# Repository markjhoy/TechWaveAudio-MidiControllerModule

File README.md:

# [TechWave Audio MIDI to CV Module](https://techwaveaudio.com/techwave-audio-mcm-100-midi-to-cv-eurorack-module/) : MCM-100

A monophonic MIDI controller Eurorack module using the Raspberry Pi Pico (RP2040).

Brought to you by [TechWave Audio](https://techwaveaudio.com)

## Features
* Single or omni MIDI channel input
* MIDI input via class-compliant USB-C or standard 5-pin MIDI cable
* Four CV outputs for note (1v/oct), Velocity, assignable Out 1 and Out 2 
  * 1v/octave through 10 octaves (at 0 to +10v), or 5 octaves (at 0 to +5v)
  * Two CV outputs with flexible routing
  * All CV outputs voltage selectable from 0v to +10v or 0 to +5v
* Expandable with additional four flexible-routed CV outputs.
* Gate, trigger, and clock full 0 to +5v outputs with divisible clock sync ticks
* Selectable note priority (last, highest, lowest)
* Tuneable pitch and velocity adjust
* Customizable trigger output duration pulse width
* Pitch bend response range from 0 to 5 octaves
* Real time display of note and output states
* Settings persist to on-board flash ROM
* 6hp wide, 3U height
* Max Power Draw:
  * +12v: 72mA (80mA with expansion) 
  * -12v: 15mA (20mA with expansion)
  * +5v: 0mA

---

### Responds to the following MIDI messages:

* **Note on / off**: sends/stops the note and velocity outputs.
  * Sends a trigger pulse on note on, and turns on the gate for the duration of the note.
  * For +10v output, responds to C-1 (note number 0) to B9 (note number 119).
  * For +5v output, responds to C2 (middle-C, note number 36) to B6 (note number 95).
* **Volume**: increases or decreases the velocity output.
* **Pitch bend**: modifies any currently playing note. Adjustable range from 0 to 5 octaves. 
* **Sustain**: holds a note on while the sustain is active.
* **Aftertouch**: selectable as an aux and/or control output.
* **Expression**: selectable as an aux and/or control output.
* **Mod wheel**: selectable as an aux and/or control output.
* **Effect 1**: selectable as an aux and/or control output.
* **Effect 2**: selectable as an aux and/or control output.
* **Start** and **Continue** sequence: selectable as an aux and/or control output.
* **Stop** sequence: selectable as an aux and/or control output.
* **Mute** (all notes off): clears any note, velocity, and gate outputs.
* **Clock tick**: MIDI clock ticks are sent directly to the `Clock` output and can be routed as an aux and/or control output.
* **Reset**: reset the MIDI input messaging queue and stops any output.

---

### Inputs

* **MIDI in**: single channel or respond to all channels (omni)
  * Both MIDI via UART and USB MIDI device in (as of v1.2.0) 
* **Menu navigation**: Five way switch (up/down, left/right, push enter)

--- 
### Outputs

* Four CV outputs:
  * **Note**: 0 to 10v output (selectable to 0 to 5v) for CV with 1v per octave.
  * **Velocity**: 0 to 10v output (selectable to 0 to 5v) for velocity / volume
  * **Out 1**: customizable CV output (0v to +10v max, selectable to 0v to +5v)
  * **Out 2**: customizable CV output (0v to +10v max, selectable to 0v to +5v)
* **Trigger**: single pulse when a note turns on, with customizable pulse on time (high / low level output)
* **Gate**: signal goes high while a note is on (high / low level output)
* **Clock**: 1ms pulse with each MIDI clock tick (high / low level output). Selectable to various clock divisions.

Using the MCM-100-EX Expansion Module, you can also add an additional four assignable CV outputs.

---

### Power

This module requires a full 16 pin (2x08 connector) standard Eurorack power connection as it uses both +/- 12v lines as well as the +5v source. 
Optional selectors in the hardware (via a DIP switch) allow the note signal to pass through to the CV bus line, and the gate signal as well.

Be certain when you plug the connector in that the orientation is the correct way, with the -12v line on the bottom (usually with the red stripe).

---

## Usage

On startup, you should see the boot screen with the current version:

The note and clock LEDs should turn on and off a few times before the dashboard screen is shown and the module is ready to be used.

The user manual can be found on the [TechWave Audio website](https://techwaveaudio.com/support/manuals/MCM-100-User_Manual.pdf).

### Dashboard

The dashboard shows the status of the current MIDI channel that it is listening on, as well as various outputs:
* The note and octave
* `vel`: The current velocity (corresponding to 0v to +10/+5v)
* `o1`: The current Out 1 value (corresponding to 0v to +10/+5v)
* `o2`: The current Out 2 value (corresponding to 0v to +10/+5v)
* Indicators for the state of the trigger, gate, and clock

If the MCM-100-EX expansion module is attached, additionally it will show:
* `x1`: The current Out X1 value (corresponding to 0v to +10/+5v)
* `x2`: The current Out X2 value (corresponding to 0v to +10/+5v)
* `x3`: The current Out X3 value (corresponding to 0v to +10/+5v)
* `x4`: The current Out X4 value (corresponding to 0v to +10/+5v)

While using the module, you can turn the dashboard display on and off via the display settings menu.
You can also adjust how often the display refreshes (set to a longer time if display events start to get dropped, shorter time for more frequent updates).

### Settings Menu

There are numerous settings available from the settings menu.
Pressing the encoder button on the dashboard display (regardless if the display is visible or not) will enter the menu.
See the [Menu System](./docs/MENU_SYSTEM.md) documentation for the menu system details.

**Note**: any settings are not persisted until you exit the menu back to the dashboard (with the exception of when resetting the settings to default).

## Building the Firmware From Source

### Prerequisites

* [Raspberry Pi Pico SDK](https://github.com/raspberrypi/pico-sdk)
* CMake
* Your favourite C++ compiler
* A compatible toolchain for building Pico firmware

### Setup

1. Initialize the Git submodules:
   1. run: `git submodule init`
   2. run: `git submodule update`
2. Copy the `.env.cmake.sample` to `.env.cmake`
3. Edit your `.env.cmake` for the following variables:
```
PICO_SDK_PATH {the path to the PICO_SDK directory)
PICO_TOOLCHAIN_PATH (path to the pico toolchain for your build machine)

# You should _not_ have to change the following
set(PICO_PLATFORM rp2040)
set(PICO_BOARD pico)
```

### Build script
```
./build.sh
```

This will run the full clean and build.

The firmware file will be put in:
```
./dist/TechWaveAudio-MCM-v2.0.0.uf2
```

## Firmware Updates

For this, you'll need a [firmware release](https://github.com/TechWave-Audio/TechWaveAudio-MidiControllerModule/releases) (or build your on locally), as well as a USB cable that has a micro-usb port on one end.

1.	Power off your rack.
2.	Remove the module from your rack but keep the module plugged in via the power cable.
3.	Download the desired firmware file version from the GitHub repository [firmware release](https://github.com/TechWave-Audio/TechWaveAudio-MidiControllerModule/releases). You only need to download the file with the .uf2 extension.
4.	Plug your USB-C cable into the jack on the front of the module and the other end into the computer with the firmware.
5.	While holding down the small boot select (BOOTSEL) button on the board, power on the module. Keep holding the boot select button until the module appears on your computer. The on-board Raspberry Pi Pico board will appear as a mass storage device, usually named “RPI-RP2”
6.	Copy the downloaded firmware .uf2 file to the storage device. When complete, the module should reboot.
7.	Power off your rack again.
8.	Disconnect your USB cable from the module and your computer. Your computer may give you a warning about the device not being properly ejected. You can safely ignore this warning.
9.	Put the module back into your rack and power back on.

Note that any settings you many have modified will be reset to any default.

## Design

## Schematic, PCB, and hardware

See the [hardware design](./docs/HARDWARE_DESIGN.md) documentation for information on the schematic and PCB design for the module.

Note - all files provided including KiCad designs and any gerber files are provided as-is and to be used at your own risk.
TechWave Audio does not guarantee the accuracy or any correctness of these files.
See the [HW_LICENSE license file](./HW_LICENSE.txt) for more, specifically the section "6 DISCLAIMER AND LIABILITY".

## Licensing

Software in this repository is licensed under the [BSD-3 License](LICENSE.txt). By using or contributing content to this repository you are agreeing to place your contributions under this license.

Hardware designs for this repository are [licensed under the CERN-OHL-S](HW_LICENSE.txt) ([CERN Open Hardware License](https://cern-ohl.web.cern.ch/)).

Parts of this repository may reference, depend on, or use compiled third party libraries. See [NOTICE.txt](NOTICE.txt) for additional details.

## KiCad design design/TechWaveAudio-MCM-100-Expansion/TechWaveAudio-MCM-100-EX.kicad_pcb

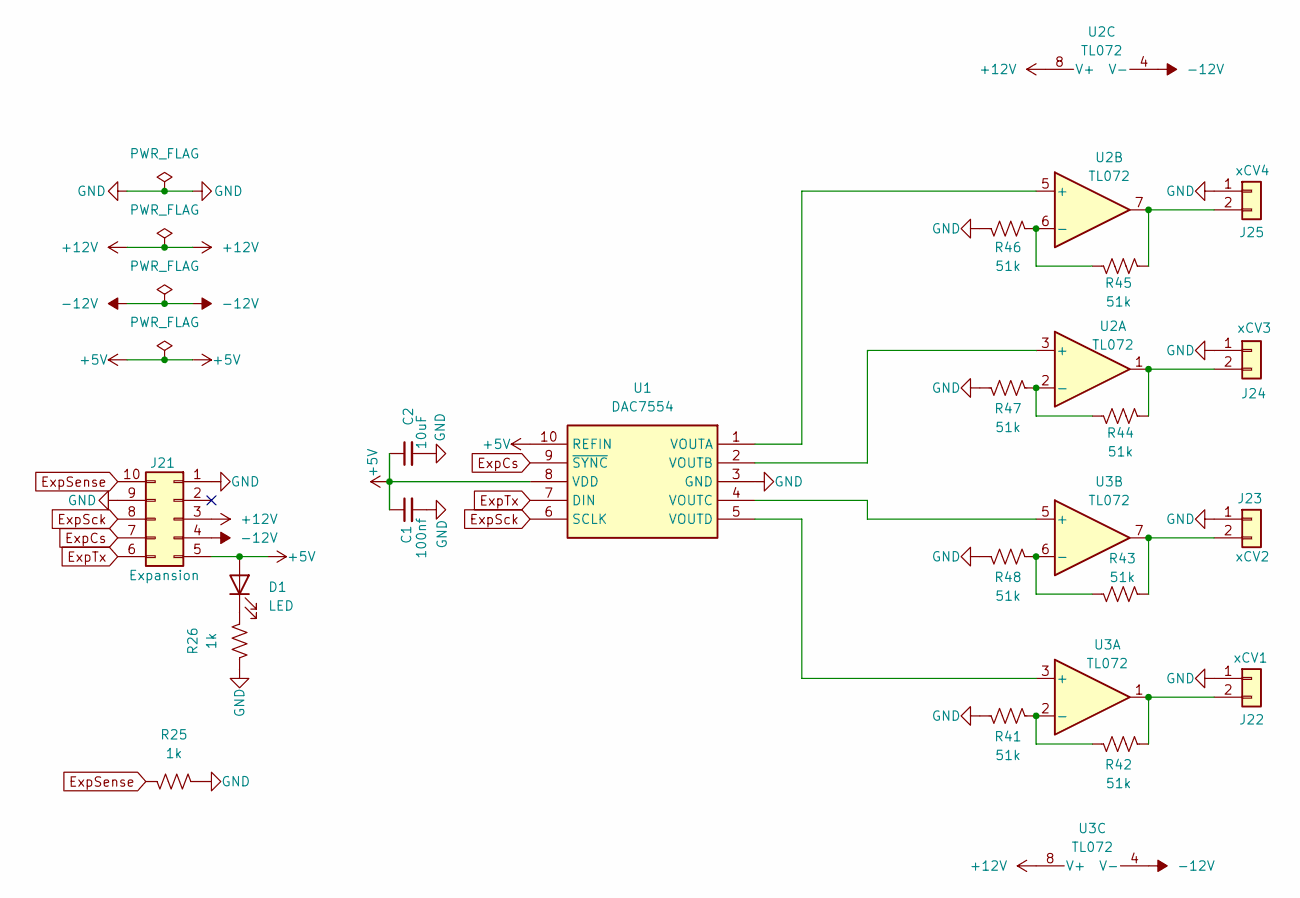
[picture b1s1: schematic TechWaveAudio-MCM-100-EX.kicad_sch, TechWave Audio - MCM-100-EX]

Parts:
C1: 100nf; C_0402_1005Metric; Voltage 1kV; Tolerance 100%
C2: 10uF; C_0805_2012Metric; Voltage 1kV; Tolerance 100%
D1: LED; LED_D3.0mm
J21: Expansion; IDC-Header_2x05_P2.54mm_Vertical
J22: xCV1; Audio_Jack_3.5mm_SameSky_SJ3-3505x
J23: xCV2; Audio_Jack_3.5mm_SameSky_SJ3-3505x
J24: xCV3; Audio_Jack_3.5mm_SameSky_SJ3-3505x
J25: xCV4; Audio_Jack_3.5mm_SameSky_SJ3-3505x
R25, R26: 1k; R_0402_1005Metric
R41, R42, R43, R44, R45, R46, R47, R48: 51k; R_0402_1005Metric
U1: DAC7554; MSOP-10_3x3mm_P0.5mm; Mouser Part Number 595-DAC7554IDGSR
U2, U3: TL072; SOIC-8_3.9x4.9mm_P1.27mm

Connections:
+5V: C1.1, C2.1, D1.2 (A), J21.5, U1.8 (VDD), U1.10 (REFIN)
+12V: J21.3, U2.8 (V+), U3.8 (V+)
-12V: J21.4, U2.4 (V-), U3.4 (V-)
ExpCs: J21.7, U1.9 (~SYNC)
ExpSck: J21.8, U1.6 (SCLK)
ExpSense: J21.10, R25.2
ExpTx: J21.6, U1.7 (DIN)
GND: C1.2, C2.2, J21.1, J21.9, J22.1, J23.1, J24.1, J25.1, R25.1, R26.2, R41.2, R46.2, R47.2, R48.2, U1.3 (GND)
unnamed: D1.1 (K), R26.1
unnamed: J22.2, R42.1, U3.1
unnamed: J23.2, R43.1, U3.7
unnamed: J24.2, R44.1, U2.1
unnamed: J25.2, R45.1, U2.7
unnamed: U1.1 (VOUTA), U2.5 (+)
unnamed: U1.2 (VOUTB), U2.3 (+)
unnamed: U1.4 (VOUTC), U3.5 (+)
unnamed: U1.5 (VOUTD), U3.3 (+)
unnamed: R44.2, R47.1, U2.2 (-)
unnamed: R45.2, R46.1, U2.6 (-)
unnamed: R41.1, R42.2, U3.2 (-)
unnamed: R43.2, R48.1, U3.6 (-)

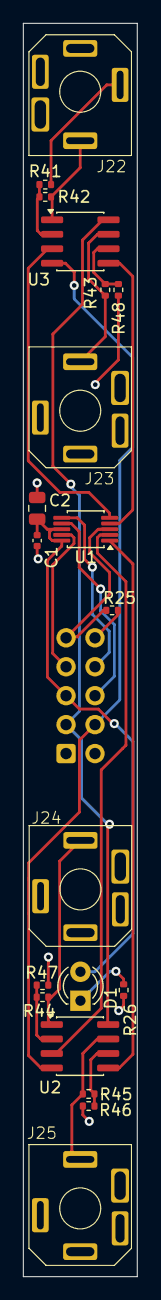
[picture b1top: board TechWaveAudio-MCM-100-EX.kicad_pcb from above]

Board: 2 copper layers, 10.0 x 110.0 mm, 21 parts (1 on the bottom side), 21 nets.

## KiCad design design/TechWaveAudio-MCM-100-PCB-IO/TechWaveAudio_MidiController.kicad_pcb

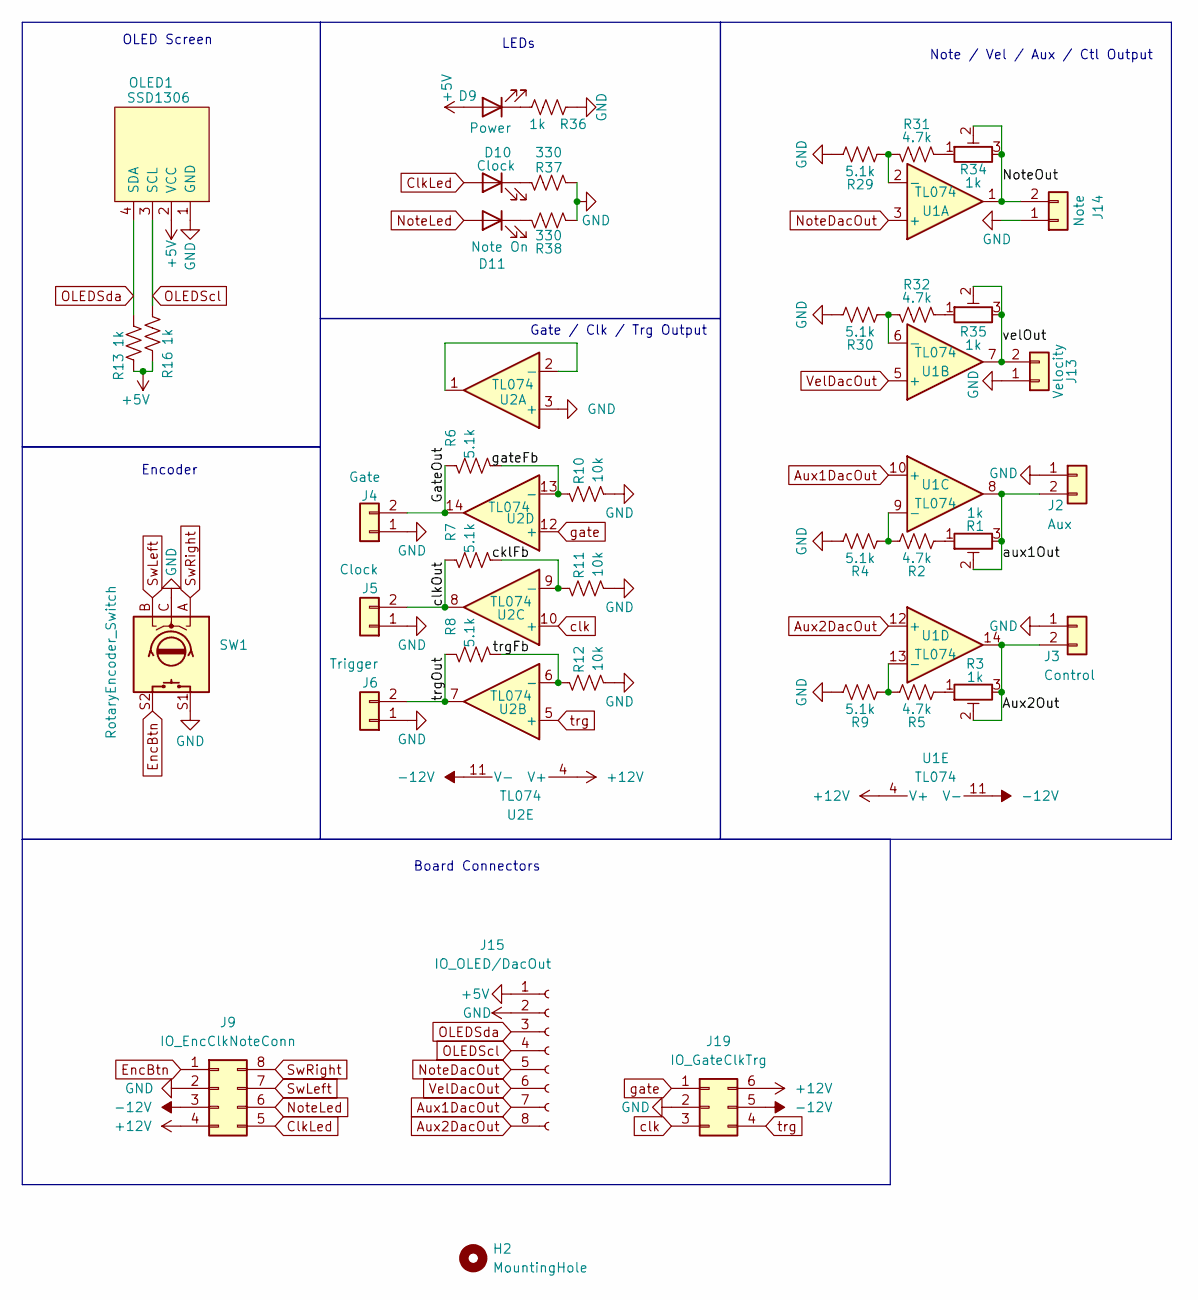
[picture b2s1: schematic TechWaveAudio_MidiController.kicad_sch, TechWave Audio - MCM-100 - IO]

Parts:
D9: Power; LED_D3.0mm
D10: Clock; LED_D3.0mm
D11: Note On; LED_D3.0mm
H2: MountingHole; MountingHole_3.2mm_M3
J2: Aux; Audio_Jack_3.5mm_SameSky_SJ3-3505x
J3: Control; Audio_Jack_3.5mm_SameSky_SJ3-3505x
J4: Gate; Audio_Jack_3.5mm_SameSky_SJ3-3505x
J5: Clock; Audio_Jack_3.5mm_SameSky_SJ3-3505x
J6: Trigger; Audio_Jack_3.5mm_SameSky_SJ3-3505x
J9: IO_EncClkNoteConn; PinSocket_2x04_P2.54mm_Vertical
J13: Velocity; Audio_Jack_3.5mm_SameSky_SJ3-3505x
J14: Note; Audio_Jack_3.5mm_SameSky_SJ3-3505x
J15: IO_OLED/DacOut; PinSocket_1x08_P2.54mm_Vertical
J19: IO_GateClkTrg; PinSocket_2x03_P2.54mm_Vertical
OLED1: SSD1306; PinSocket_1x04_P2.54mm_Vertical
R1, R3, R34, R35: 1k; Potentiometer_Bourns_3296X_Horizontal
R2, R5, R31, R32: 4.7k; R_0402_1005Metric
R4, R6, R7, R8, R9, R29, R30: 5.1k; R_0402_1005Metric
R10, R11, R12: 10k; R_0402_1005Metric
R13, R16, R36: 1k; R_0402_1005Metric
R37, R38: 330; R_0402_1005Metric
SW1: RotaryEncoder_Switch; Rotary_Encoder-PEC11-Breakout_Board
U1, U2: TL074; SOIC-14_3.9x8.7mm_P1.27mm

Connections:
+5V: D9.2 (A), J15.2, OLED1.2 (VCC), R13.1, R16.1
+12V: J9.4, J19.6, U1.4 (V+), U2.4 (V+)
-12V: J9.3, J19.5, U1.11 (V-), U2.11 (V-)
/Aux2Out: J3.2, R3.2, R3.3, U1.14
/GateOut: J4.2, R6.1, U2.14
/NoteOut: J14.2, R34.2, R34.3, U1.1
/aux1Out: J2.2, R1.2, R1.3, U1.8
/cklFb: R7.2, R11.1, U2.9 (-)
/clkOut: J5.2, R7.1, U2.8
/gateFb: R6.2, R10.1, U2.13 (-)
/trgFb: R8.2, R12.1, U2.6 (-)
/trgOut: J6.2, R8.1, U2.7
/velOut: J13.2, R35.2, R35.3, U1.7
Aux1DacOut: J15.7, U1.10 (+)
Aux2DacOut: J15.8, U1.12 (+)
ClkLed: D10.2 (A), J9.5
EncBtn: J9.1, SW1.S2
GND: J2.1, J3.1, J4.1, J5.1, J6.1, J9.2, J13.1, J14.1, J15.1, J19.2, OLED1.1 (GND), R4.1, R9.1, R10.2, R11.2, R12.2, R29.1, R30.1, R36.2, R37.2, R38.2, SW1.C, SW1.S1, U2.3 (+)
unnamed: D9.1 (K), R36.1
unnamed: D10.1 (K), R37.1
unnamed: D11.1 (K), R38.1
unnamed: R1.1, R2.2
unnamed: R3.1, R5.2
unnamed: R31.2, R34.1
unnamed: R32.2, R35.1
unnamed: R29.2, R31.1, U1.2 (-)
unnamed: R30.2, R32.1, U1.6 (-)
unnamed: R2.1, R4.2, U1.9 (-)
unnamed: R5.1, R9.2, U1.13 (-)
unnamed: U2.1, U2.2 (-)
NoteDacOut: J15.5, U1.3 (+)
NoteLed: D11.2 (A), J9.6
OLEDScl: J15.4, OLED1.3 (SCL), R16.2
OLEDSda: J15.3, OLED1.4 (SDA), R13.2
SwLeft: J9.7, SW1.B
SwRight: J9.8, SW1.A
VelDacOut: J15.6, U1.5 (+)
clk: J19.3, U2.10 (+)
gate: J19.1, U2.12 (+)
trg: J19.4, U2.5 (+)

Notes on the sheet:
Board Connectors
Note / Vel / Aux / Ctl Output
Encoder
Gate / Clk / Trg Output
OLED Screen
LEDs

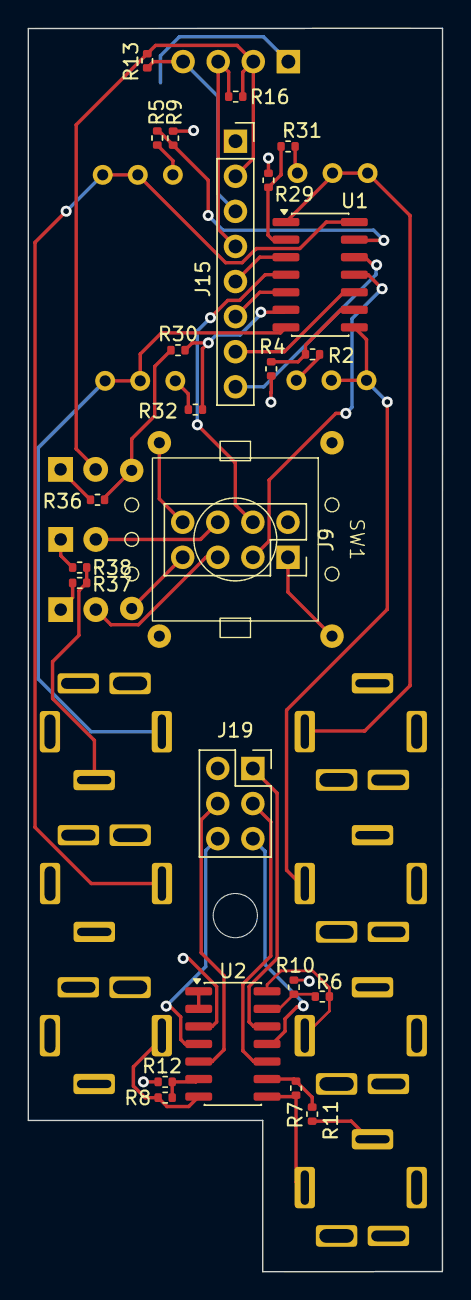
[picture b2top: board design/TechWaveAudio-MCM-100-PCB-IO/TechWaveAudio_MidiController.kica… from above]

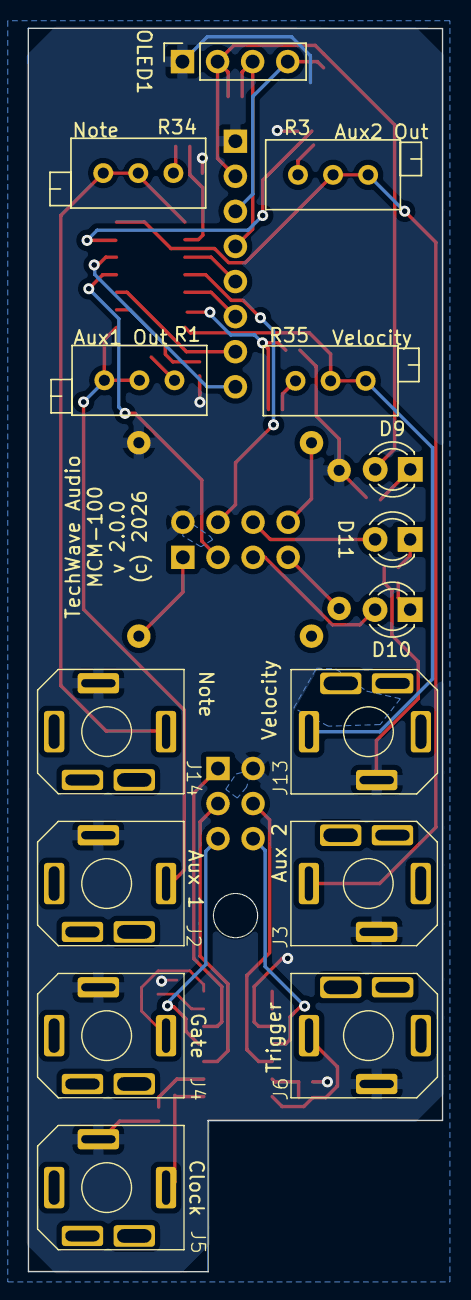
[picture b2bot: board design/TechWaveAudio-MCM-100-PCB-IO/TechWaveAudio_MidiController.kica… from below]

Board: 2 copper layers, 30.0 x 90.0 mm, 41 parts (15 on the bottom side), 40 nets.

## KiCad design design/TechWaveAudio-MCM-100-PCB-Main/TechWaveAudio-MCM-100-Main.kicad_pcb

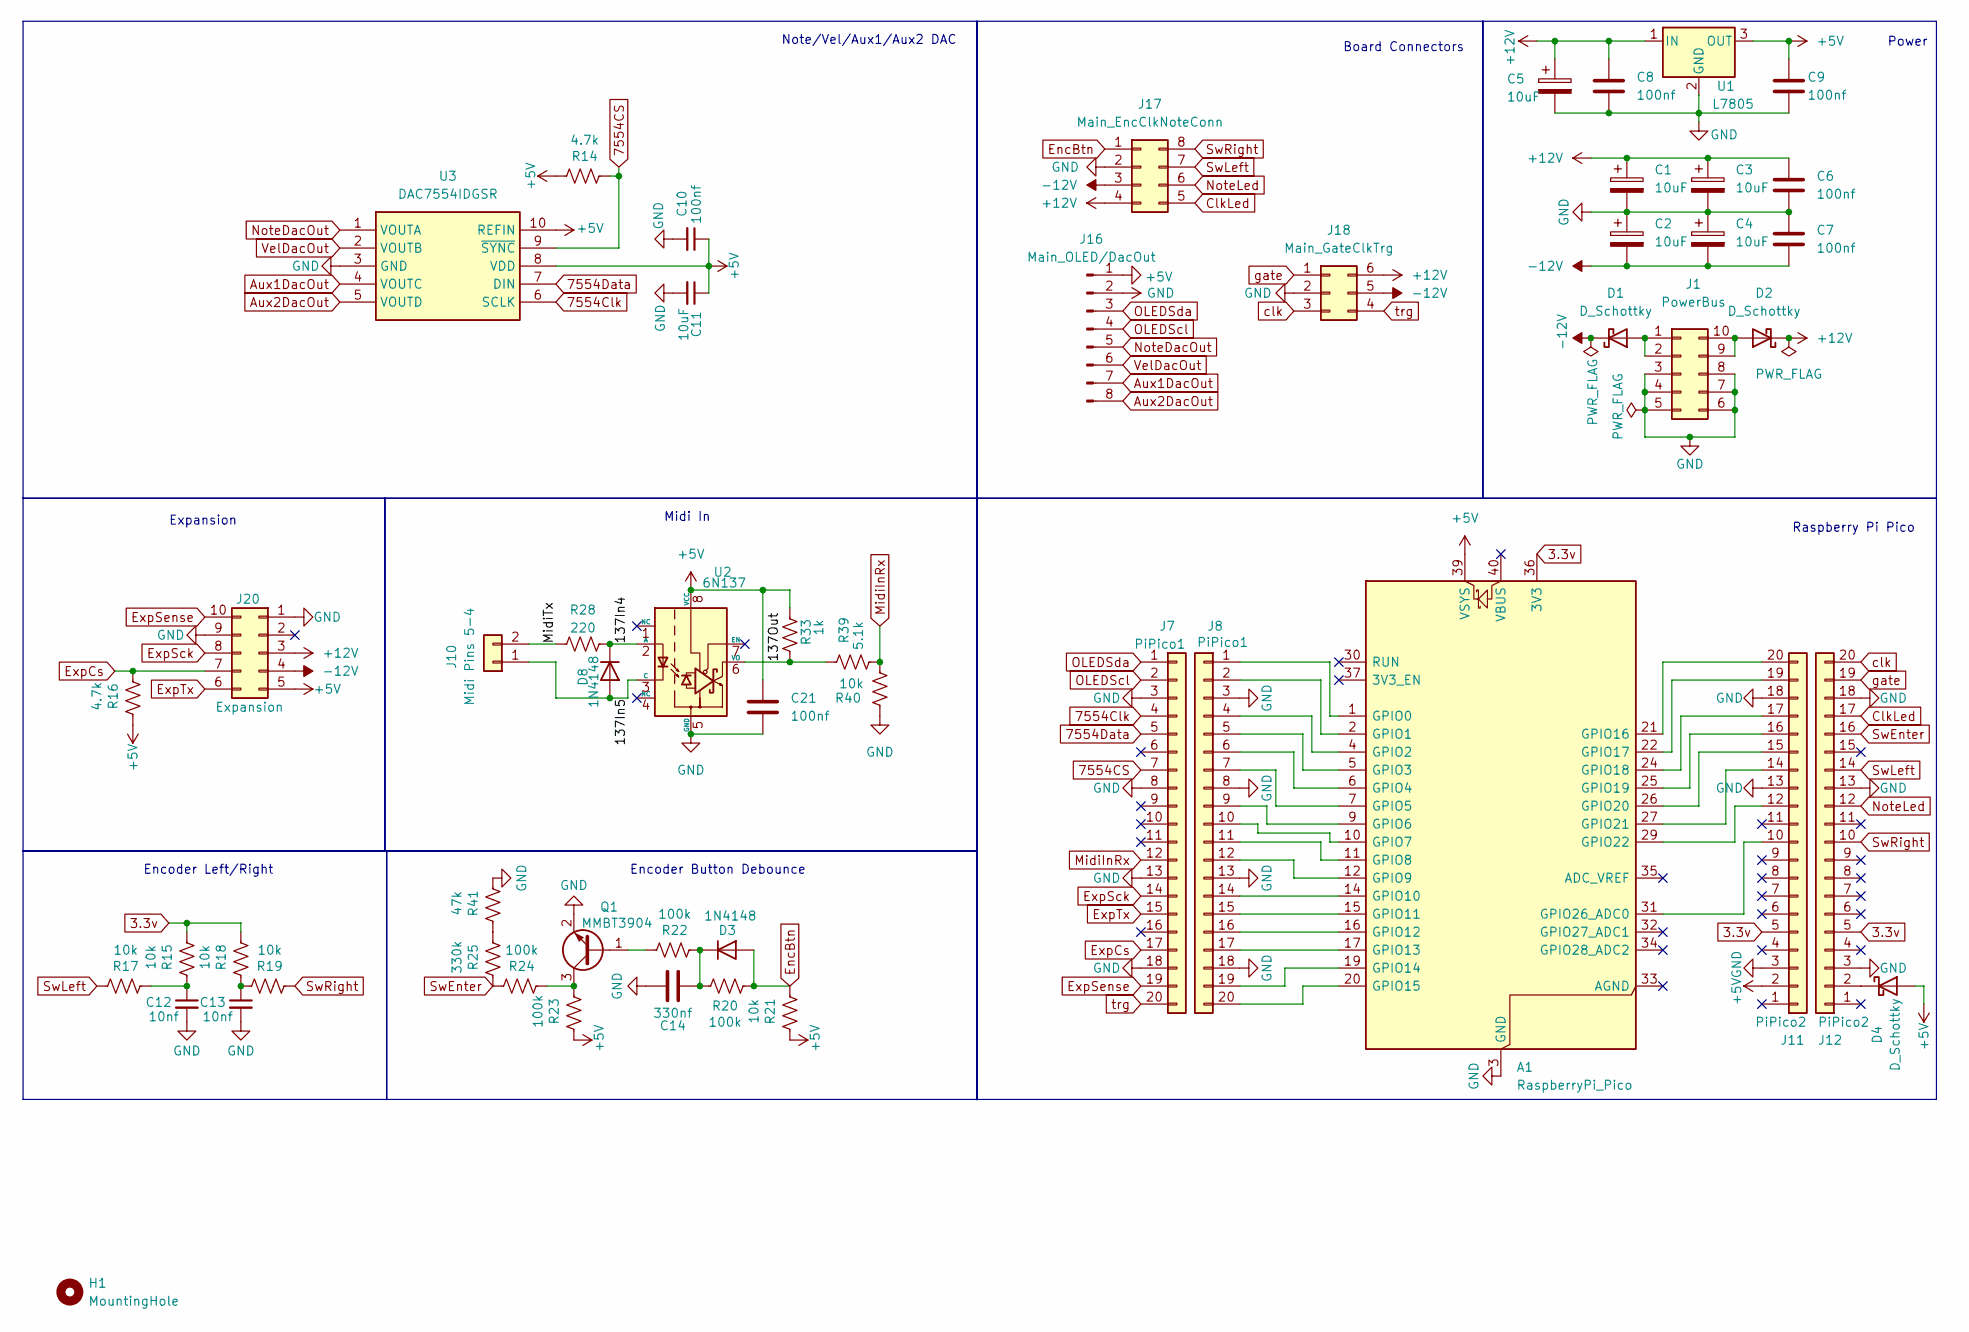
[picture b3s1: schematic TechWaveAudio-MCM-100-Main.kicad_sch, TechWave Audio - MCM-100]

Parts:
A1: RaspberryPi_Pico; DIP-40_W15.24mm_Socket
C1, C2, C3, C4, C5: 10uF; CP_EIA-6032-28_Kemet-C
C6, C7, C8, C9, C21: 100nf; C_0402_1005Metric
C10: 100nf; C_0402_1005Metric; Voltage 1kV; Tolerance 100%
C11: 10uF; C_0805_2012Metric; Voltage 1kV; Tolerance 100%
C12, C13: 10nf; C_0402_1005Metric; Voltage 1kV; Tolerance 100%
C14: 330nf; C_0402_1005Metric
D1, D2, D4: D_Schottky; D_0805_2012Metric
D3, D8: 1N4148; D_SOD-323
H1: MountingHole; MountingHole_3.2mm_M3
J1: PowerBus; IDC-Header_2x05_P2.54mm_Vertical
J7: PiPico1; PinHeader_1x20_P2.54mm_Vertical
J8: PiPico1
J10: Midi Pins 5-4; PinHeader_1x02_P2.54mm_Vertical
J11: PiPico2
J12: PiPico2; PinHeader_1x20_P2.54mm_Vertical
J16: Main_OLED/DacOut; PinHeader_1x08_P2.54mm_Vertical
J17: Main_EncClkNoteConn; PinHeader_2x04_P2.54mm_Vertical
J18: Main_GateClkTrg; PinHeader_2x03_P2.54mm_Vertical
J20: Expansion; PinHeader_2x05_P2.54mm_Vertical
Q1: MMBT3904; SOT-23
R14, R16: 4.7k; R_0402_1005Metric
R15, R17, R18, R19, R21, R40: 10k; R_0402_1005Metric
R20, R22, R23, R24: 100k; R_0402_1005Metric
R25: 330k; R_0402_1005Metric
R28: 220; R_0402_1005Metric
R33: 1k; R_0402_1005Metric
R39: 5.1k; R_0402_1005Metric
R41: 47k; R_0402_1005Metric
U1: L7805; SOT-223-3_TabPin2
U2: 6N137; DIP-8_W7.62mm
U3: DAC7554IDGSR; TSSOP-10_3x3mm_P0.5mm; Mouser Part Number 595-DAC7554IDGSR

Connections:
3.3v: A1.36 (3V3), J11.5, J12.5, R15.2, R18.2
7554CS: J7.7, R14.2, U3.9 (~SYNC)
7554Clk: J7.4, U3.6 (SCLK)
7554Data: J7.5, U3.7 (DIN)
+5V: A1.39 (VSYS), C9.1, C10.1, C11.1, C21.1, D4.2 (A), J11.2, J16.2, J20.5, R14.1, R16.1, R21.1, R23.1, R33.2, U1.3 (OUT), U2.8 (VCC), U3.8 (VDD), U3.10 (REFIN)
+12V: C1.1, C3.1, C5.1, C6.1, C8.1, D2.1 (K), J17.4, J18.6, J20.3, U1.1 (IN)
/137In4: D8.1 (K), R28.2, U2.2 (A)
/137In5: D8.2 (A), J10.1, U2.3 (C)
/137Out: R33.1, R39.1, U2.6 (VO)
/MidiTx: J10.2, R28.1
Aux1DacOut: J16.7, U3.4 (VOUTC)
Aux2DacOut: J16.8, U3.5 (VOUTD)
ClkLed: J12.17, J17.5
EncBtn: D3.2 (A), J17.1, R20.1, R21.2
ExpCs: J7.17, J20.7, R16.2
ExpSck: J7.14, J20.8
ExpSense: J7.19, J20.10
ExpTx: J7.15, J20.6
GND: A1.3 (GND), A1.8 (GND), A1.13 (GND), A1.18 (GND), A1.23 (GND), A1.28 (GND), A1.38 (GND), C1.2, C2.1, C3.2, C4.1, C5.2, C6.2, C7.1, C8.2, C9.2, C10.2, C11.2, C12.2, C13.2, C14.1, C21.2, J1.3, J1.4, J1.5, J1.6, J1.7, J1.8, J7.3, J7.8, J7.13, J7.18, J8.3, J8.8, J8.13, J8.18, J11.3, J11.13, J11.18, J12.3, J12.13, J12.18, J16.1, J17.2, J18.2, J20.1, J20.9, Q1.2 (E), R40.1, R41.2, U1.2 (GND), U2.5 (GND), U3.3 (GND)
MidiInRx: J7.12, R39.2, R40.2
unnamed: A1.1 (GPIO0), J8.1
unnamed: A1.2 (GPIO1), J8.2
unnamed: A1.4 (GPIO2), J8.4
unnamed: A1.5 (GPIO3), J8.5
unnamed: A1.6 (GPIO4), J8.6
unnamed: A1.7 (GPIO5), J8.7
unnamed: A1.9 (GPIO6), J8.9
unnamed: A1.10 (GPIO7), J8.10
unnamed: A1.11 (GPIO8), J8.11
unnamed: A1.12 (GPIO9), J8.12
unnamed: A1.14 (GPIO10), J8.14
unnamed: A1.15 (GPIO11), J8.15
unnamed: A1.16 (GPIO12), J8.16
unnamed: A1.17 (GPIO13), J8.17
unnamed: A1.19 (GPIO14), J8.19
unnamed: A1.20 (GPIO15), J8.20
unnamed: A1.21 (GPIO16), J11.20
unnamed: A1.22 (GPIO17), J11.19
unnamed: A1.24 (GPIO18), J11.17
unnamed: A1.25 (GPIO19), J11.16
unnamed: A1.26 (GPIO20), J11.15
unnamed: A1.27 (GPIO21), J11.14
unnamed: A1.29 (GPIO22), J11.12
unnamed: A1.31 (GPIO26_ADC0), J11.10
unnamed: C12.1, R15.1, R17.2
unnamed: C13.1, R18.1, R19.1
unnamed: D2.2 (A), J1.9, J1.10
unnamed: C14.2, D3.1 (K), R20.2, R22.2
unnamed: D4.1 (K), J12.2
unnamed: Q1.1 (B), R22.1
unnamed: Q1.3 (C), R23.2, R24.2
unnamed: R25.2, R41.1
NoteDacOut: J16.5, U3.1 (VOUTA)
NoteLed: J12.12, J17.6
OLEDScl: J7.2, J16.4
OLEDSda: J7.1, J16.3
SwEnter: J12.16, R24.1, R25.1
SwLeft: J12.14, J17.7, R17.1
SwRight: J12.10, J17.8, R19.2
VelDacOut: J16.6, U3.2 (VOUTB)
clk: J12.20, J18.3
gate: J12.19, J18.1
trg: J7.20, J18.4

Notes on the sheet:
Encoder Button Debounce
Note/Vel/Aux1/Aux2 DAC
Midi In
Power
Expansion
Raspberry Pi Pico
Encoder Left/Right
Board Connectors

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
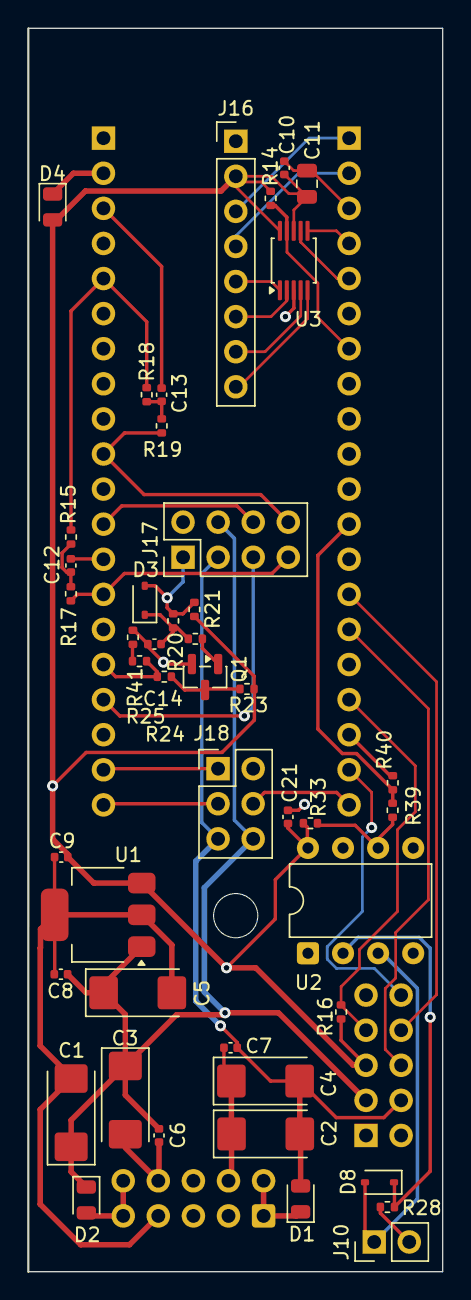
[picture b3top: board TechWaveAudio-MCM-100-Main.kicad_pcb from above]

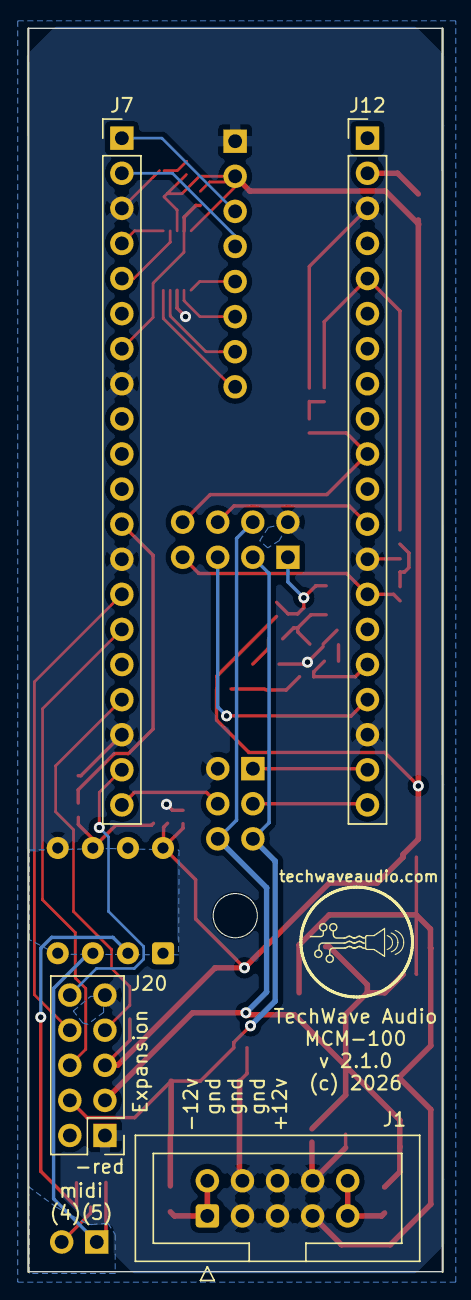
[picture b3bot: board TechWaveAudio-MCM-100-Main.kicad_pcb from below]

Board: 2 copper layers, 30.0 x 90.0 mm, 50 parts (4 on the bottom side), 41 nets.

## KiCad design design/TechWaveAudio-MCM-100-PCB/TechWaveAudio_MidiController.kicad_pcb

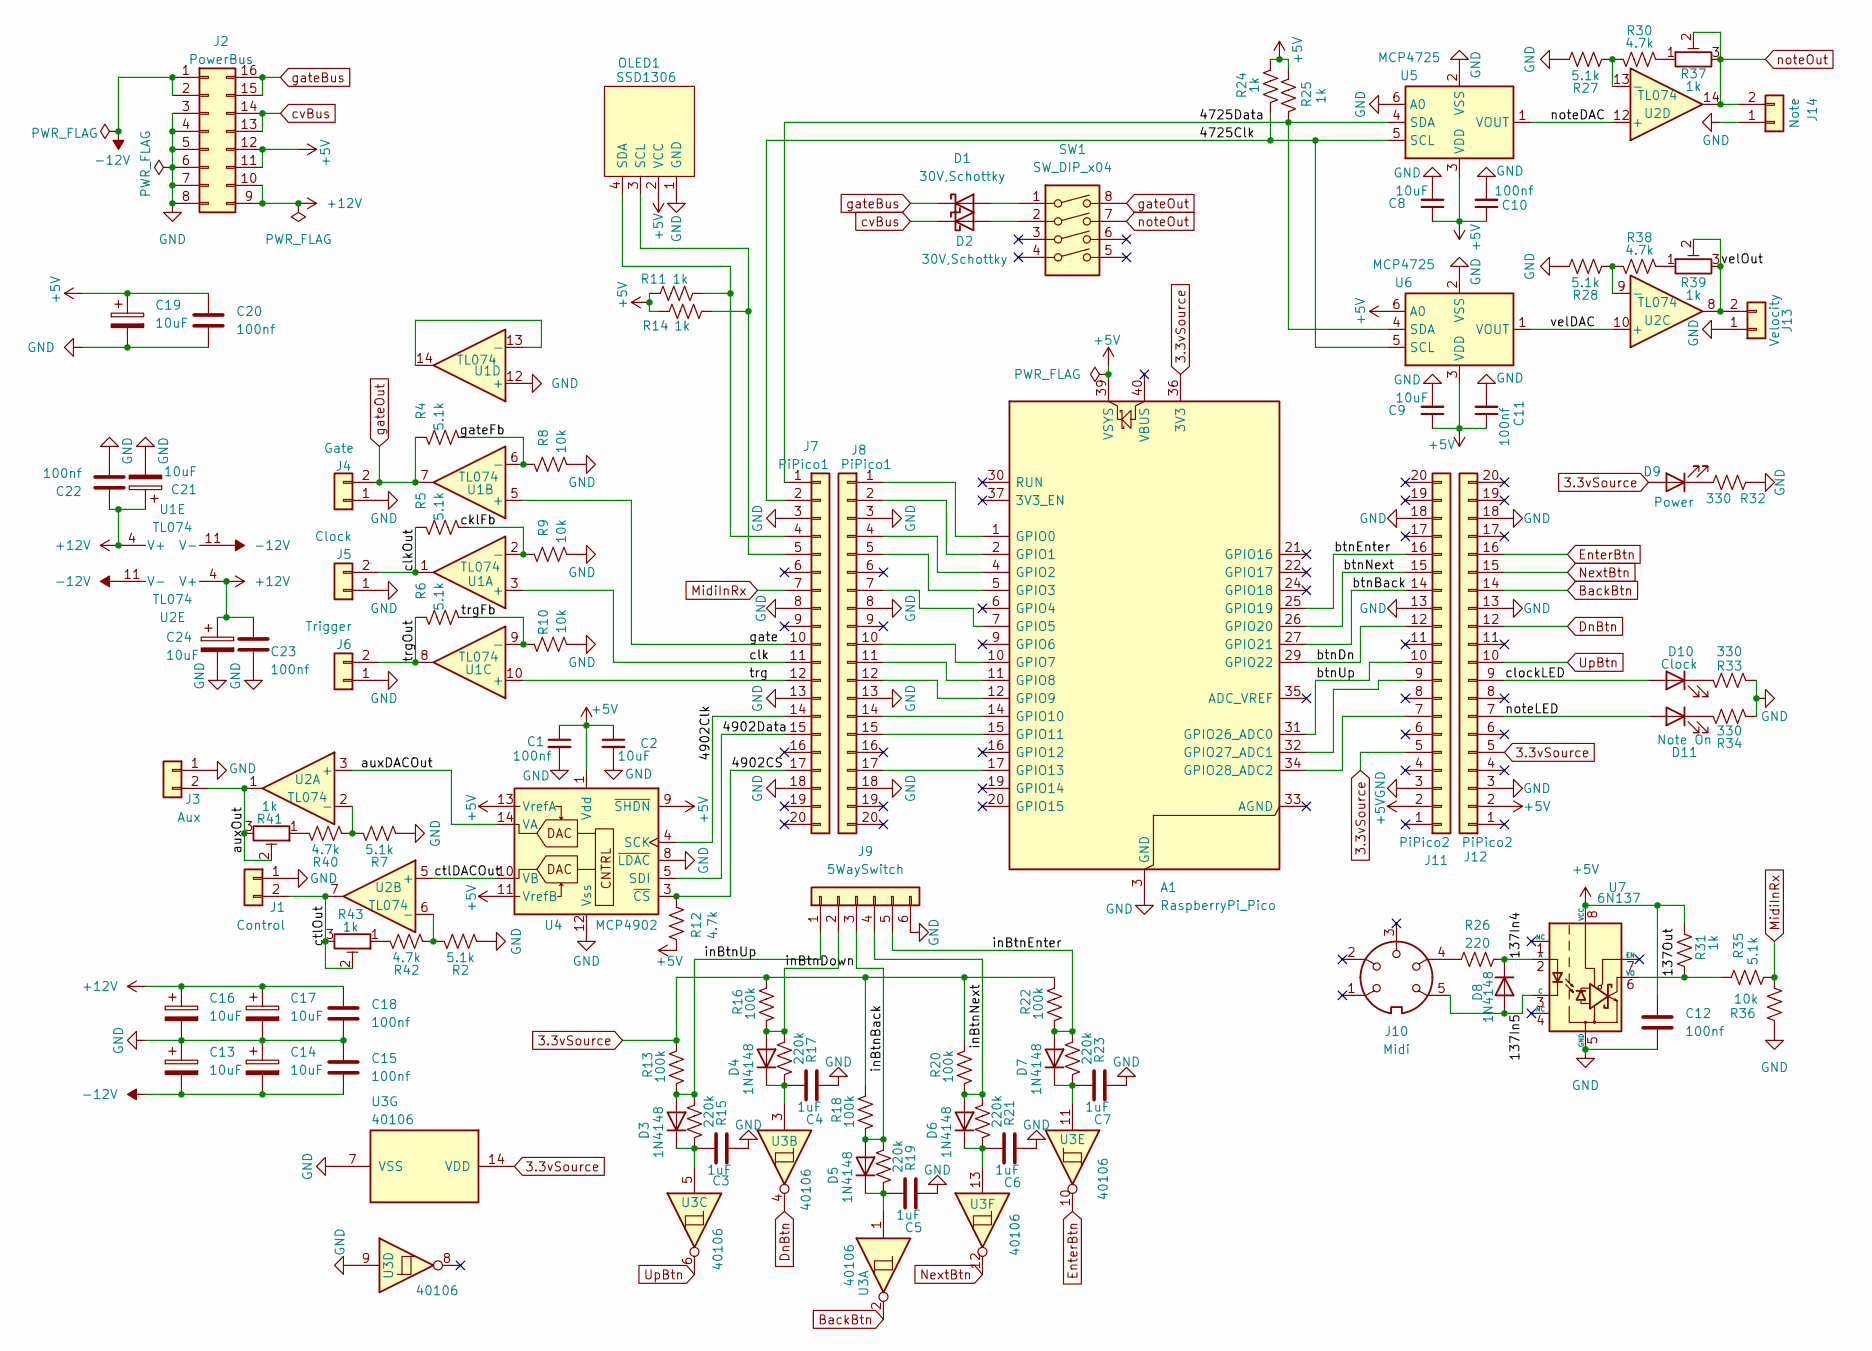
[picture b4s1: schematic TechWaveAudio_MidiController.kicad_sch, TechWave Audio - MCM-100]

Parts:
A1: RaspberryPi_Pico; DIP-40_W15.24mm_Socket
C1, C10, C11: 100nf; C_0402_1005Metric; Voltage 1kV; Tolerance 100%
C2, C8, C9: 10uF; C_0805_2012Metric; Voltage 1kV; Tolerance 100%
C3, C4, C5, C6, C7: 1uF; C_0402_1005Metric
C12, C15, C18, C20, C22, C23: 100nf; C_0402_1005Metric
C13, C14, C16, C17, C19, C21, C24: 10uF; C_0805_2012Metric
D1, D2: 30V,Schottky; SOT-23
D3, D4, D5, D6, D7, D8: 1N4148; D_SOD-323
D9: Power; LED_Rectangular_W5.0mm_H2.0mm
D10: Clock; LED_Rectangular_W5.0mm_H2.0mm
D11: Note On; LED_Rectangular_W5.0mm_H2.0mm
J1: Control; Jack_3.5mm_SameSky_SJ3-3505x
J2: PowerBus; IDC-Header_2x08_P2.54mm_Vertical
J3: Aux; Jack_3.5mm_SameSky_SJ3-3505x
J4: Gate; Jack_3.5mm_SameSky_SJ3-3505x
J5: Clock; Jack_3.5mm_SameSky_SJ3-3505x
J6: Trigger; Jack_3.5mm_SameSky_SJ3-3505x
J7: PiPico1; PinSocket_1x20_P2.54mm_Vertical
J8: PiPico1
J9: 5WaySwitch; PinSocket_1x06_P2.54mm_Vertical
J10: Midi; PinHeader_1x05_P2.54mm_Vertical
J11: PiPico2
J12: PiPico2; PinSocket_1x20_P2.54mm_Vertical
J13: Velocity; Jack_3.5mm_SameSky_SJ3-3505x
J14: Note; Jack_3.5mm_SameSky_SJ3-3505x
OLED1: SSD1306; PinSocket_1x04_P2.54mm_Vertical
R2, R4, R5, R6, R7, R27, R28, R35: 5.1k; R_0402_1005Metric
R8, R9, R10, R36: 10k; R_0402_1005Metric
R11, R14, R24, R25, R31: 1k; R_0402_1005Metric
R12, R30, R38, R40, R42: 4.7k; R_0402_1005Metric
R13, R16, R18, R20, R22: 100k; R_0402_1005Metric
R15, R17, R19, R21, R23: 220k; R_0402_1005Metric
R26: 220; R_0402_1005Metric
R32, R33, R34: 330; R_0402_1005Metric
R37, R39, R41, R43: 1k; Potentiometer_Bourns_3296X_Horizontal
SW1: SW_DIP_x04; DIP-8_W7.62mm
U1, U2: TL074; SOIC-14_3.9x8.7mm_P1.27mm
U3: 40106; TSSOP-14_4.4x5mm_P0.65mm
U4: MCP4902; TSSOP-14_4.4x5mm_P0.65mm
U5, U6: MCP4725; SOT-23-6
U7: 6N137; DIP-8_W7.62mm

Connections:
3.3vSource: A1.36 (3V3), D9.2 (A), J11.5, J12.5, R13.2, R16.2, R18.2, R20.2, R22.2, U3.14 (VDD)
+5V: A1.39 (VSYS), C1.1, C2.1, C8.1, C9.1, C10.1, C11.1, C12.1, C19.1, C20.1, J2.11, J2.12, J11.2, J12.2, OLED1.2 (VCC), R11.1, R12.2, R14.1, R24.1, R25.1, R31.2, U4.1 (Vdd), U4.9 (~SHDN), U4.11 (VrefB), U4.13 (VrefA), U5.3 (VDD), U6.3 (VDD), U6.6 (A0), U7.8 (VCC)
+12V: C16.1, C17.1, C18.1, C21.1, C22.1, C23.1, C24.1, J2.9, J2.10, U1.4 (V+), U2.4 (V+)
-12V: C13.2, C14.2, C15.2, J2.1, J2.2, U1.11 (V-), U2.11 (V-)
/137In4: D8.1 (K), R26.2, U7.2 (A)
/137In5: D8.2 (A), J10.5, U7.3 (C)
/137Out: R31.1, R35.1, U7.6 (VO)
/4725Clk: J7.2, R24.2, U5.5 (SCL), U6.5 (SCL)
/4725Data: J7.1, R25.2, U5.4 (SDA), U6.4 (SDA)
/4902CS: J7.17, R12.1, U4.3 (~CS)
/4902Clk: J7.14, U4.4 (SCK)
/4902Data: J7.15, U4.5 (SDI)
/auxDACOut: U2.3 (+), U4.14 (VA)
/auxOut: J3.2, R41.2, R41.3, U2.1
/cklFb: R5.2, R9.1, U1.2 (-)
/clk: J7.11, U1.3 (+)
/clkOut: J5.2, R5.1, U1.1
/clockLED: D10.2 (A), J12.9
/ctlDACOut: U2.5 (+), U4.10 (VB)
/ctlOut: J1.2, R43.2, R43.3, U2.7
/gate: J7.10, U1.5 (+)
/gateFb: R4.2, R8.1, U1.6 (-)
/inBtnBack: D5.2 (A), J9.3, R18.1, R19.1
/inBtnDown: D4.2 (A), J9.2, R16.1, R17.1
/inBtnEnter: D7.2 (A), J9.5, R22.1, R23.1
/inBtnNext: D6.2 (A), J9.4, R20.1, R21.1
/inBtnUp: D3.2 (A), J9.1, R13.1, R15.1
/noteDAC: U2.12 (+), U5.1 (VOUT)
/noteLED: D11.2 (A), J12.7
/trg: J7.12, U1.10 (+)
/trgFb: R6.2, R10.1, U1.9 (-)
/trgOut: J6.2, R6.1, U1.8
/velDAC: U2.10 (+), U6.1 (VOUT)
/velOut: J13.2, R39.2, R39.3, U2.8
BackBtn: J12.14, U3.2
DnBtn: J12.12, U3.4
EnterBtn: J12.16, U3.10
GND: A1.3 (GND), A1.8 (GND), A1.13 (GND), A1.18 (GND), A1.23 (GND), A1.28 (GND), A1.38 (GND), C1.2, C2.2, C3.1, C4.1, C5.1, C6.1, C7.1, C8.2, C9.2, C10.2, C11.2, C12.2, C13.1, C14.1, C15.1, C16.2, C17.2, C18.2, C19.2, C20.2, C21.2, C22.2, C23.2, C24.2, J1.1, J2.3, J2.4, J2.5, J2.6, J2.7, J2.8, J3.1, J4.1, J5.1, J6.1, J7.3, J7.8, J7.13, J7.18, J8.3, J8.8, J8.13, J8.18, J9.6, J11.3, J11.13, J11.18, J12.3, J12.13, J12.18, J13.1, J14.1, OLED1.1 (GND), R2.1, R7.1, R8.2, R9.2, R10.2, R27.1, R28.1, R32.2, R33.2, R34.2, R36.1, U1.12 (+), U3.7 (VSS), U3.9, U4.8 (~LDAC), U4.12 (Vss), U5.2 (VSS), U5.6 (A0), U6.2 (VSS), U7.5 (GND)
MidiInRx: J7.7, R35.2, R36.2
unnamed: A1.1 (GPIO0), J8.1
unnamed: A1.2 (GPIO1), J8.2
unnamed: A1.4 (GPIO2), J8.4
unnamed: A1.5 (GPIO3), J8.5
unnamed: A1.7 (GPIO5), J8.7
unnamed: A1.10 (GPIO7), J8.10
unnamed: A1.11 (GPIO8), J8.11
unnamed: A1.12 (GPIO9), J8.12
unnamed: A1.14 (GPIO10), J8.14
unnamed: A1.15 (GPIO11), J8.15
unnamed: A1.17 (GPIO13), J8.17
unnamed: A1.25 (GPIO19), J11.16
unnamed: A1.26 (GPIO20), J11.15
unnamed: A1.27 (GPIO21), J11.14
unnamed: A1.29 (GPIO22), J11.12
unnamed: A1.31 (GPIO26_ADC0), J11.10
unnamed: A1.32 (GPIO27_ADC1), J11.9
unnamed: A1.34 (GPIO28_ADC2), J11.7
unnamed: D1.2 (A), SW1.1
unnamed: D2.2 (A), SW1.2
unnamed: C3.2, D3.1 (K), R15.2, U3.5
unnamed: C4.2, D4.1 (K), R17.2, U3.3
unnamed: C5.2, D5.1 (K), R19.2, U3.1
unnamed: C6.2, D6.1 (K), R21.2, U3.13
unnamed: C7.2, D7.1 (K), R23.2, U3.11
unnamed: D9.1 (K), R32.1
unnamed: D10.1 (K), R33.1
unnamed: D11.1 (K), R34.1
unnamed: J7.4, OLED1.4 (SDA), R11.2
unnamed: J7.5, OLED1.3 (SCL), R14.2
unnamed: J10.4, R26.1
unnamed: R30.2, R37.1
unnamed: R38.2, R39.1
unnamed: R40.2, R41.1
unnamed: R42.2, R43.1
unnamed: U1.13 (-), U1.14
unnamed: R7.2, R40.1, U2.2 (-)
unnamed: R2.2, R42.1, U2.6 (-)
unnamed: R28.2, R38.1, U2.9 (-)
unnamed: R27.2, R30.1, U2.13 (-)
NextBtn: J12.15, U3.12
UpBtn: J12.10, U3.6
cvBus: D2.1 (K), J2.13, J2.14
gateBus: D1.1 (K), J2.15, J2.16
gateOut: J4.2, R4.1, SW1.8, U1.7
noteOut: J14.2, R37.2, R37.3, SW1.7, U2.14

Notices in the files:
design/TechWaveAudio-MCM-100-PCB/TechWaveAudio_MidiController.kicad_pcb:
(c) 2026 TechWave Audio
